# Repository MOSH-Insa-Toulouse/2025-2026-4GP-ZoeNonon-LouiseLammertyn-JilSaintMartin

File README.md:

# 2025-2026-4GP-ZoeNonon-LouiseLammertyn-JilSaintMartin
### Introduction

Dans le cadre de la formation en Génie Physique de l'INSA Toulouse, les étudiants de 4ème année doivent réaliser un capteur low-tech à base de graphite et en faire une analyse critique. Le but final étant de répondre à la question suivante:  

<p align="center">
  <strong>Un capteur graphite low-tech peut-il remplacer un flexeur commercial ?</strong>
</p>

Ce capteur graphitte se base sur les travaux de:

  - [1]	K.-H. Müller, J. Herrmann, B. Raguse, G. Baxter, and T. Reda, “Percolation model for electron conduction in films of metal nanoparticles linked by organic molecules,” Phys. Rev. B, vol. 66, no. 7, p. 075417, Aug. 2002, doi: 10.1103/PhysRevB.66.075417.
  
  - [2]	C.-W. Lin, Z. Zhao, J. Kim, and J. Huang, “Pencil Drawn Strain Gauges and Chemiresistors on Paper,” Sci. Rep., vol. 4, no. 1, p. 3812, Jan. 2014, doi: 10.1038/srep03812.
  
  - [3]	K.-H. Müller, J. Herrmann, G. Wei, B. Raguse, and L. Wieczorek, “Electron transport in nanoparticle assemblies,” in 2010 International Conference on Nanoscience and Nanotechnology, Feb. 2010, pp. 316–318. doi: 10.1109/ICONN.2010.6045236.

### Description du projet 
Le capteur de contrainte en graphite repose sur un réseau conducteur de particules de graphite déposées sur un substrat en papier.
Lorsque l'on trace un trait au crayon sur du papier, les particules de graphite adhèrent aux fibres, formant ainsi un mince film conducteur.
Ce film se comporte comme un système granulaire désordonné où la conduction électrique s'effectue par le biais des contacts entre les particules de graphite.
La déformation mécanique affecte ce réseau :
  - Sous contrainte de traction, la distance entre les particules augmente, ce qui réduit les contacts électriques et augmente la résistance.
  - Sous contrainte de compression, les particules sont rapprochées, ce qui améliore la connectivité et diminue la résistance.

La réponse du capteur est donc régie par les variations du réseau et les effets de tunnel entre particules voisines.
En raison de sa structure, le capteur est très sensible aux petites déformations, mais il est également influencé par des paramètres de fabrication tels que la densité du graphite, la dureté du crayon et les conditions environnementales (humidité, température).

<p align="center">
  <em>Echelle évaluant la dureté de différentes mines de crayons</em>
</p>

**La variation de résistance qui en résulte peut être mesurée à l'aide d'un circuit à transimpédance, afin d'obtenir un signal analogique.**

Ce projet se divise en plusieurs étapes décrites ci-dessous. 

<p align="center">
  <em>Logo du capteur graphite "GraphiFlop"</em>
</p>

### Livrables
Pour valider ce projet nous devons proposer: 
- Un circuit imprimé (PCB) pour créer les circuits électroniques reliant nos composants
- Un code arduino qui permet de contrôler un ARDUINO afin de mesurer la résistance du capteur, faire nos tests et contrôler des éléments tels que le bluetooth, l'écran ou l'encodeur rotatoire
- Une datasheet présentant les caractéristiques du capteur graphite fabriqué
- Une application ANDROID permettant de recevoir les données par bluetooth et les afficher sur un graphique

### Matériel
Afin de réaliser ce capteur, nous utilisons le matériel suivant: 

- Une carte Arduino UNO
- Un écran OLED (I2C)
- Un potentiomètre numérique MCP41050
- Un encodeur rotatoire
- Un capteur de déformation en papier low tech
- Un module bluetooth

Pour réaliser l'amplificateur transimpédance, nous avons utilisé: 

- Un amplificateur opérationnel LTC1050
- Deux condensateurs de 100nF
- Un condensateur de 1µF
- Deux résistances de 100kΩ
- Deux résistances de 1kΩ
- Une résistance de 10kΩ

### LTspice
La première étape de se projet est de simuler le circuit d'amplification transimpédance du capteur sur LTspice. 
Le  montage est un amplificateur à transimpédance (TIA) basé sur l’AOP LTC1050.

Le principe du montage est de convertir le courant traversant le capteur en une tension exploitable. L’amplificateur opérationnel, configuré en transimpédance, permet d’obtenir une tension de sortie proportionnelle à la valeur de la résistance.

Un filtre passe-bas est ajouté en sortie afin de réduire le bruit et de fournir un signal stable, compatible avec une entrée analogique.

Dans la suite du projet, R2 sera remplacée par un potentiomètre numérique, afin de permettre la calibration de l’Arduino sur une plage de tension comprise entre 0 et 5 V.

<p align="center">
  <em>Circuit d'amplification transimpédance sur LTspice</em>
</p>

Pour consulter les différents fichiers, aller à [2.LTSpice](https://github.com/MOSH-Insa-Toulouse/2025-2026-4GP-ZoeNonon-LouiseLammertyn-JilSaintMartin/tree/main/2.LTSpice)

### Kicad

Une fois la simulation validée sur LTspice, l'étape suivante consiste à transformer le schéma théorique en un objet physique fonctionnel : le Circuit Imprimé (PCB). 
Pour ce faire, nous utilisons la suite logicielle KiCad.

Cette phase de conception se décompose en trois étapes majeures :

**Saisie schématique et empreinte**

La première étape consiste à reproduire le circuit de l’amplificateur transimpédance.
- Intégration des composants: Nous y plaçons l'AOP LTC1050, les composants passifs (résistances, condensateurs) et les connecteurs nécessaires à l'Arduino Uno, l'écran OLED et l'encodeur rotatif.
- Association des empreintes: Chaque symbole schématique est lié à une empreinte physique réelle. Cette étape est cruciale pour assurer que les composants pourront être soudés correctement sur le cricuit final.

<p align="center">
  <em>Visualisation de la schématique du montage sur KiCad</em>
</p>

**Routage et placement**

Le passage au routage permet de définir la disposition physique des éléments sur la carte de cuivre.
- Placement des composants et routages: Nous avons disposé les composants afin de pouvoir router par la suite le plus efficacement possible, sans que les composants et les pistes ne se superposent.
- Plan de masse: Un plan de masse a été intégré pour stabiliser les potentiels et réduire le bruit sur le circuit analogique.

<p align="center">
  <em>Visualisation du routage du montage sur KiCad</em>
</p>

**Visualisation 3D et vérification**

Enfin, KiCad permet une modélisation 3D du projet. Cet outil nous a permis de:
- Vérifier l'encombrement mécanique des composants.
- Valider la cohérence globale avant la fabrication du PCB.

<p align="center">
  <em>Visualisation 3D du montage global sur KiCad</em>
</p>

Pour consulter les différents fichiers, aller à [3.KiCad](https://github.com/MOSH-Insa-Toulouse/2025-2026-4GP-ZoeNonon-LouiseLammertyn-JilSaintMartin/tree/main/3.KiCad)

### Fabrication PCB et soudage

<p align="center">
  <em>Fichier généré par KiCad pour l'impression du PCB</em>
</p>

Une fois le routage validé sous KiCad et le fichier de perçage généré, nous avons pu imprimer notre circuit électronique (merci Cathy <3). Ensuite, nous avons percé et soudé le montage complet. Avant de passer au code Arduino, nous avons vérifié que tout fonctionnait bien à l'aide d'un multimètre, en effectuant les étapes suivantes:
- Vérification que chaque piste relie bien les bons points du schéma.
- Absence totale de court-circuit entre le 5V et le GND.

<p align="center">
  <em>Face arrière du PCB</em>
</p>

### Arduino
Il a ensuite été nécessaire de réaliser un code arduino afin de pouvoir contrôler la carte. Ce code permet notamment d'effectuer les mesures sur le capteur graphite et de contrôler les différents composants tels que le module bluetooth, l'écran OLED et l'encodeur rotatoire. 

**Mesure**

La première partie du code est dédiée à la mesure de la tension aux bornes du capteur. A l'aide d'une fonction, la tension mesurée permet de déduire la résistance du capteur. 

Une fonction de calibration a aussi été créee afin de calibrer la tension aux bornes du capteur. Comme l'arduino UNO permet de délivrer une tension entre 0V et 5V, il est intéressant de régler le potentiomètre numérique afin que la tension aux bornes du capteur lorsque le capteur n'est pas tordu, soit de 2,5V. Ce potentiomètre numérique remplace dans le montage électronique la résistance R2.

Notre montage permet aussi d'utiliser un flexor commercial. Pour cela, une fonction au sein du code permet de mesurer la tension différement et d'en déduire la résistance. La calibration n'est cependant pas nécessaire sur ce capteur. 

<p align="center">
  <em>Flexor commercial</em>
</p>

La lecture de tension aux bornes du capteur graphite ou du flexor commercial s'effectue toutes les 100ms. 

**Composants pour l'utilisateur**

<p align="center">
  <em>Schéma des différents composants</em>
</p>

Le reste du code permet de gérer le reste des composants. Une fonction permet de gérer l'affichage sur l'écran OLED. Sur cet écran, l'affichage d'un menu permet d'intéragir avec l'utilisateur. Une fonction gère l'encodeur rotatoire qui permet à l'utilisateur de se déplacer sur le menu. Enfin, une dernière fonction permet d'envoyer les données mesurées à l'aide du module bluetooth sur un téléphone connecté. 

<p align="center">
  <em>Menu affiché sur l'écran OLED</em>
</p>

Pour consulter les différents fichiers, aller à [4.Arduino](https://github.com/MOSH-Insa-Toulouse/2025-2026-4GP-ZoeNonon-LouiseLammertyn-JilSaintMartin/tree/main/4.Arduino)

### Application
A l'aide du site internet "MIT App Inventor", nous avons pu créer une interface pour téléphone ANDROID sur laquelle l'arduino UNO peut communiquer des données par bluetooth. Le code de cette application se base sur l'empilage de blocs de code. 

Le code traite d'abord la communication avec le module bluetooth de l'arduino en s'assurant que les données reçues sont bien des valeurs numériques positives. Une fois les données réceptionnées, les données sont affichées sur un graphique qui se met à jour en continu. 

L'application permet par ailleurs d'afficher le mode de mesure en cours (mesure de tension ou de résistance) ainsi que le capteur utilisé. 

<p align="center">
  <em>Interface de l'application GraphiFlop</em>
</p>

Pour consulter les différents fichiers, aller à [5.Application](https://github.com/MOSH-Insa-Toulouse/2025-2026-4GP-ZoeNonon-LouiseLammertyn-JilSaintMartin/tree/main/5.Application)

### Banc de tests
Pour cette partie, nous avons utilisé un banc de test conçu par les groupes précédents.

<p align="center">
  <em>Banc de test</em>
</p>

Afin de vérifier les résultats obtenus, nous avons tracé la variation relative de la résistance du capteur en fonction de la déformation mécanique. La résistance relative est mesurée pour chaque courbure du banc de test.
La déformation peut être calculée à partir de la géométrie du dispositif selon la relation suivante :

Ensuite, à l’aide du code arduino, nous avons mesuré la résistance du capteur pour quatre types de crayons différents. Une mesure de référence à plat a d’abord été réalisée, puis des mesures ont été effectuées pour différentes courbures du banc de test, en compression et en tension.
La résistance relative est définie par :

Pour consulter les différents fichiers, aller à [6.Banc de tests](https://github.com/MOSH-Insa-Toulouse/2025-2026-4GP-ZoeNonon-LouiseLammertyn-JilSaintMartin/tree/main/6.Banc%20de%20tests)
### Résulats
Nous avons obtenu les courbes suivantes :

On observe que les résultats obtenus en flexion présentent une relation globalement linéaire entre la déformation et la variation de résistance. Le capteur est donc particulièrement adapté à la mesure de flexion. Cependant la durée de vie du capteur est courte les valeurs sont tres vraibale lorsque que celui ci a deja été pliée. 
On retrouve bien les résultats attendus concernant la sensibilité du capteur en fonction du grade du crayon. Les crayons "tendres" (ex : 6B, à forte concentration en graphite) présentent une sensibilité plus faible que les crayons plus "durs" (ex : HB). 

Cela s’explique par la structure du réseau conducteur : une plus forte densité de graphite rend le chemin de conduction plus stable, ce qui réduit l’amplitude relative des variations de résistance lors des déformations.
En revanche, les résultats en compression sont moins concluants. Bien que les courbes restent globalement affines, la variation de résistance n’est pas entièrement exploitable : le signal tend à revenir vers la résistance au repos lorsque le capteur est courbé.

Ce comportement peut s’expliquer par un phénomène mécanique : en compression, la couche de graphite entre en contact avec le banc de test, entraînant une perte de matière  et une modification irréversible du réseau conducteur.

Enfin, nous n’avons pas réussi à obtenir de mesures exploitables avec les crayons H et 2H, car le signal électrique généré était trop faible pour être détecté par le système de mesure.

Pour consulter les différents fichiers, aller à [7.Datasheet](https://github.com/MOSH-Insa-Toulouse/2025-2026-4GP-ZoeNonon-LouiseLammertyn-JilSaintMartin/tree/main/7.Datasheet)

### Erreur rencontré
Au cours de ce projet, de nombreuse erreurs ont été rencontrées, que nous détaillons ci-dessous. 

Les premiers problèmes rencontrés sont liés à une erreur de routage sur KiCad. En effet, nous avons vite remarqué que certains composants n'étaient pas reliés au bonnes pins de l'arduino comme par exemple le potentiomètre numérique. Nous avons aussi oublié d'ajouter sur le PCB initial des broches afin de connecter le flexor commercial ou bien une capacité associée à l'encodeur rotatoire. Nous avons cependant pu remédier à ces erreurs en ressoudant avec des fils certaines pistes du PCB (encore merci Cathy :)).

<p align="center">
  <em>Face arrière du PCB (après réparation)</em>
</p>

Nous avons aussi rencontré des problèmes quant aux codes écrits lors de ce projet. En effet, nous avons fait face à des problèmes de RAM de l'écran OLED. Nous avons pu cependant régler ce problème. Par ailleurs, nous avons aussi eu des difficultés face à la fonction de calibration qui ne fonctionne pas toujours ou bien face à certaines boucles de l'application ANDROID qui ne sont pas toujours lues. Nous n'avons malheureusement pas pu remédier à ces problèmes. 

Enfin, nous avons rencontré des difficultés quant au capteur en lui-même. Le capteur graphite a, comme expliqué précédemment, une durée de vie assez courte ce qui rend difficile certaines mesures.

### Conclusion
Ce capteur est fiable comme le montre les courbes réalisées. Il permet d'effectuer des mesurer tant en flexion qu'en compression (ce qui n'est pas le cas pour un flexor commercial) avec une sensibilité certaine. 
Un avantage considérable du capteur graphite est son prix très bas en comparaison d'un capteur commercial. 

Cependant, la durée de vie du capteur est courte ce qui le rend peut réutilisable. 

Pour conclure, ce capteur graphite est commercialisable à condition de pouvoir augmenter sa durée de vie. On pourrait par exemple proposer l'ajout d'une couche de protection sur le capteur afin d'éviter d'enlever du graphite ainsi que d'utiliser un papier moins fragile. 

<p align="center">
  <strong>GraphiFlop c'est validé! 😎👍</strong>
</p>

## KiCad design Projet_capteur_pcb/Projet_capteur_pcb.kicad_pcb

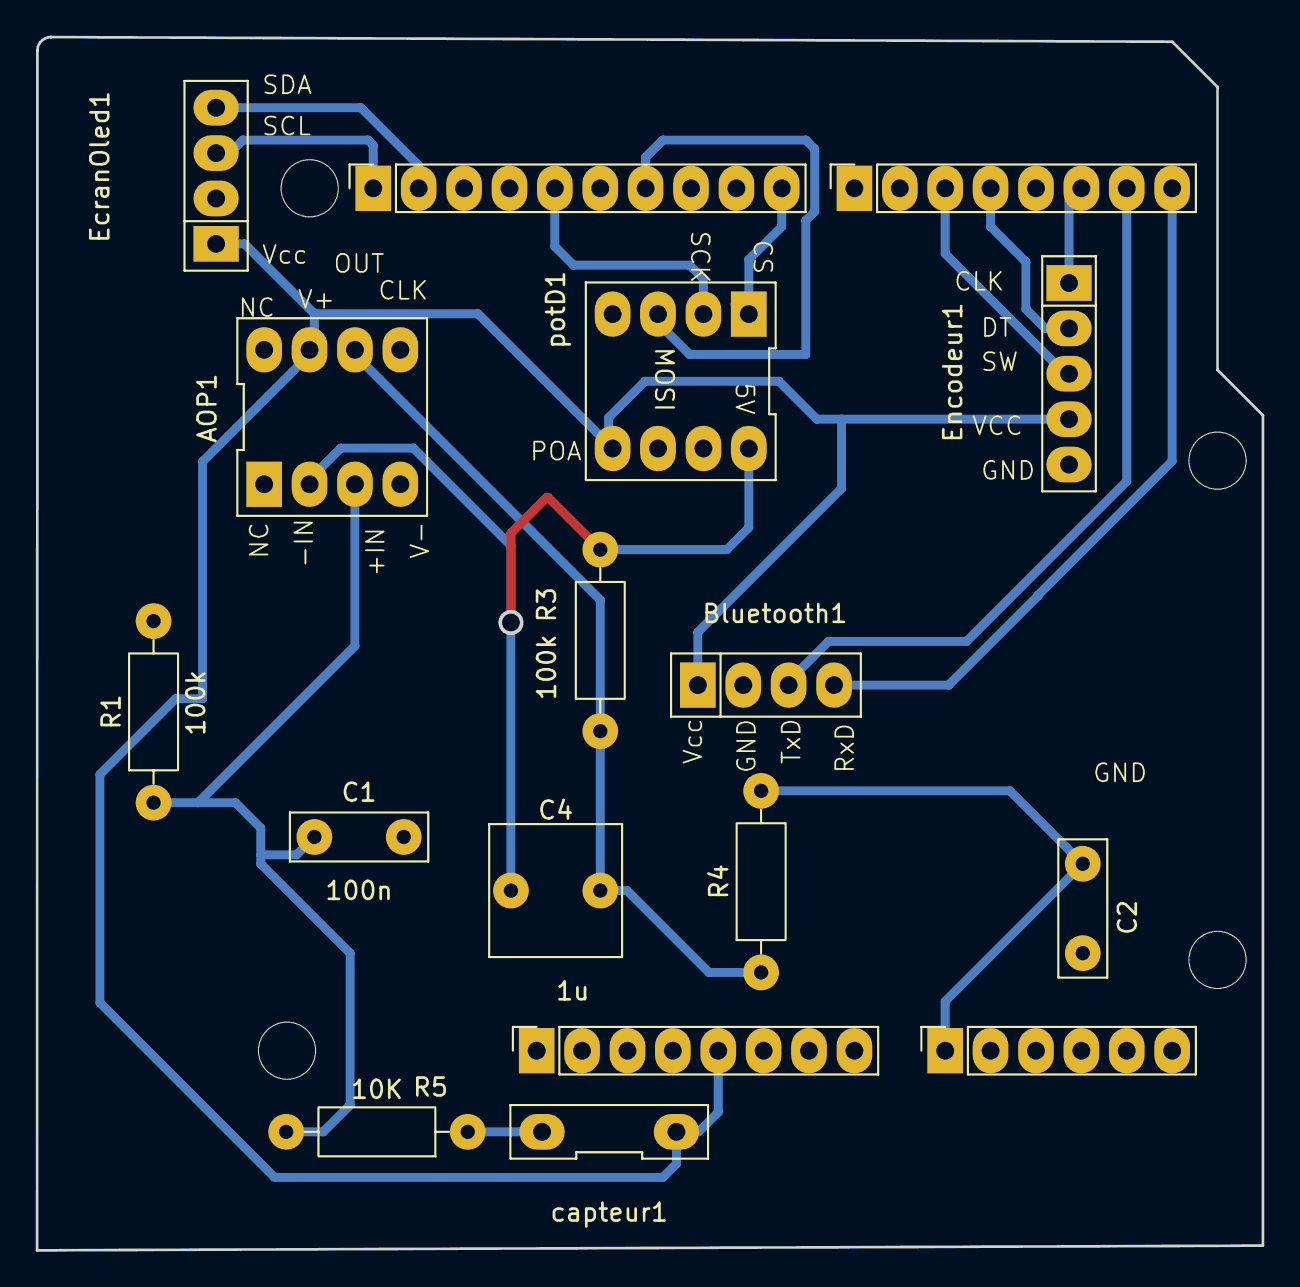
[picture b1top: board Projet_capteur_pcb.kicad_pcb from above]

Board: 2 copper layers, 68.6 x 67.9 mm, 21 parts (0 on the bottom side), 17 nets.

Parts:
AOP1: AO
Bluetooth1: Empreinte_bluetooth
C1, C2: 100n; C_Disc_D7.5mm_W2.5mm_P5.00mm
C4: 1u; C_Rect_L7.2mm_W7.2mm_P5.00mm_FKS2_FKP2_MKS2_MKP2
EcranOled1: EcranOled
Encodeur1: ENCODEUR
J1: Power; PinSocket_1x08_P2.54mm_Vertical
J2: Digital/PWM; PinSocket_1x10_P2.54mm_Vertical
J3: Analog; PinSocket_1x06_P2.54mm_Vertical
J4: Digital/PWM; PinSocket_1x08_P2.54mm_Vertical
MH1, MH2, MH3, MH4: MountingHole_3.2mm
R1, R3: 100k; R_Axial_DIN0207_L6.3mm_D2.5mm_P10.16mm_Horizontal
R4: 1k; R_Axial_DIN0207_L6.3mm_D2.5mm_P10.16mm_Horizontal
R5: 10K; R_Axial_DIN0207_L6.3mm_D2.5mm_P10.16mm_Horizontal
capteur1: DIP-2_296_ELL
potD1: dig pot

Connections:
+5V: AOP1.7 (V+), Bluetooth1.1 (Vcc), EcranOled1.1 (Vcc), Encodeur1.4 (VCC), J1.5, capteur1.1 (IN), potD1.5 (VDD)
CLK: Encodeur1.1 (CLK), J4.6
CS: J2.10, potD1.1 (CS)
DT: Encodeur1.2 (DT), J4.4
GND: AOP1.4 (V-), Bluetooth1.2 (GND), C1.2, C2.2, EcranOled1.2 (GND), Encodeur1.5 (GND), J1.6, J1.7, J2.4, R1.2, potD1.4 (Vss), potD1.6 (PBO), potD1.7 (PW0)
MOSI: J2.7, potD1.3 (SI)
unnamed: AOP1.3 (+IN), C1.1, R1.1, R5.2
unnamed: AOP1.6 (OUT), C4.2, R3.1, R4.1
unnamed: R5.1, capteur1.2 (OUT)
Rxd: Bluetooth1.4 (RxD), J4.8
SCK: J2.5, potD1.2 (SCK)
SCL: EcranOled1.3 (SCL), J2.1, J3.6
SDA: EcranOled1.4 (SDA), J2.2, J3.5
SW: Encodeur1.3 (SW), J4.3
TxD: Bluetooth1.3 (TxD), J4.7
ampli_out: C2.1, J3.1, R4.2
potor_out: AOP1.2 (-IN), C4.1, R3.2, potD1.8 (PA0)

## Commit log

2026-02-10 reponse
2026-02-10 j'accepte
2026-02-24 projet capteur dans le main
2026-02-24 3D + placement
2026-02-24 Create explications_photo with project photo guidelines
    Added instructions for photo organization in the project.
2026-02-24 Create explicationkicad
2026-02-24 Add import and screenshot instructions
    Add instructions for importing application files and taking screenshots.
2026-02-24 Create fiche
2026-02-24 Update emphasis on key question in README
2026-02-24 Fix link format for LTspice section in README
2026-02-24 Fix link formatting in README.md
2026-02-28 routageV1 modif
2026-03-05 routageV1
2026-03-06 fichier_gerber
2026-03-06 nouveau zip
2026-03-09 changement-dim-pad
2026-03-11 chepa
2026-03-17 rangement
2026-03-17 ajout encodeur
2026-03-17 potentiometre
2026-04-08 datasheet
2026-04-08 interface
2026-04-09 readme
2026-04-09 ajoutphoto
2026-04-09 lt spice
    Corrected typos and improved clarity in the LTspice section.
2026-04-09 Update README with KiCad PCB design information
    Added details about the PCB design process using KiCad.
2026-04-09 Revise component list and add PCB images in README
    Updated the list of components used for the transimpedance amplifier and added images of the PCB.
2026-04-09 Enhance Kicad section with PCB design steps
    Updated the Kicad section to provide detailed steps for PCB design, including schematic entry, routing, and 3D visualization.
2026-04-09 uadgiu
2026-04-09 oython
2026-04-09 python
2026-04-09 ezjdpz
2026-04-12 Enhance README with images and Arduino details
    Updated images and improved Arduino section for clarity.
2026-04-12 Change section headers from '##' to '#####'
    Updated section headers in README.md for clarity and consistency.
2026-04-12 Revise headings and descriptions in README
    Updated section headings and descriptions for clarity.
2026-04-12 photo
2026-04-12 Refactor Arduino code for sensor calibration and display
2026-04-12 code final
2026-04-13 grpahique
2026-04-13 Rename code2.ino.ino to derniere_version.ino
2026-04-16 datasheet+banc de test
2026-04-16 bancdetest
2026-04-16 Fix formatting and spelling in README.md
    Corrected formatting and spelling errors in the README, including section titles and descriptions for clarity.
2026-04-16 dkjnqzd
2026-04-16 Rename Code_arduino_rpojet_capteur.ino to Code_arduino_projet_capteur.ino
2026-04-16 Rename main.pdf to Datasheet.pdf
2026-04-17 datashette
2026-05-14 Create test
2026-05-14 Rename shm.png to schema_kicad.png
2026-05-14 Rename pcb.png to pcb_kicad.png
2026-05-14 references
2026-05-14 description projet
2026-05-14 bon jusquà la partie 3
2026-05-14 image
2026-05-14 Fix image tag formatting for PCB visualization
    Updated the image tag for PCB visualization in README.
2026-05-14 Update README with 3D visualization section
    Added a section for 3D visualization and verification.
2026-05-14 centre image
2026-05-14 Enhance README with centered routing visualization text
    Added a centered paragraph for routing visualization in KiCad.
2026-05-14 Correct HTML tags in README.md
    Fixed HTML formatting in the README file.
2026-05-14 couleur
2026-05-14 Modify PCB routing visualization caption
    Updated the caption for the PCB routing visualization to use emphasis formatting.
2026-05-14 Update sensor question formatting in README
2026-05-14 test couleur
2026-05-14 Change table cell background color in README
2026-05-14 Update README with PCB fabrication details and images
    Removed unnecessary table and added image with caption for PCB fabrication section.
2026-05-14 arduino
2026-05-14 photos
2026-05-14 Fix image dimensions for Flexor in README
    Correct the image dimensions for the Flexor in the README.
2026-05-14 Update README with test results and images
    Added images and results for resistance measurements based on mechanical deformation.
2026-05-14 Update README with project details and images
    Added images and additional details about the project components and processes.
2026-05-14 Change logo image height in README
    Updated logo image size in README.
2026-05-14 Adjust logo size in README
    Updated logo image dimensions in README.md.
2026-05-14 Fix image dimensions in README
    Updated image dimensions in README.md for clarity.
2026-05-14 Enhance README with application details and images
    Added images and detailed application functionality for the Android interface using MIT App Inventor.
2026-05-14 final
    Update test bench section and correct typos in README.
2026-05-14 Change emphasis to strong for GraphiFlop validation
